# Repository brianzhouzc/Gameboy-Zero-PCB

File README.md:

This is the project page for the Gameboy Zero Button PCB.

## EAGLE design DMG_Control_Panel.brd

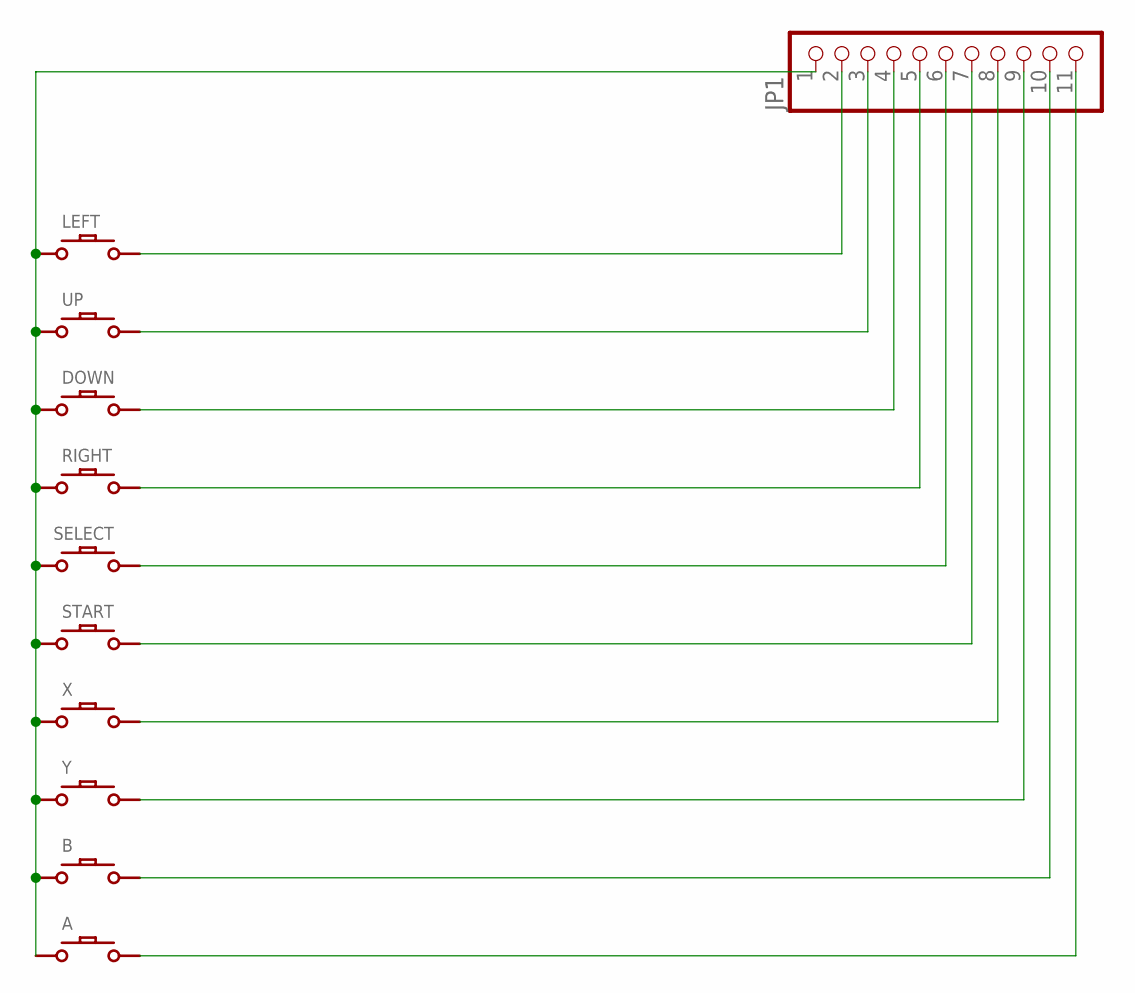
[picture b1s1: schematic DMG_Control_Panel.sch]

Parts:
A: DMG-BTN
B: DMG-BTN
DOWN: DMG-BTN
JP1: PINHD-1X11M; 1X11M
LEFT: DMG-BTN
RIGHT: DMG-BTN
SELECT: DMG-BTN; DMG-SEL
START: DMG-BTN; DMG-SEL
UP: DMG-BTN
X: DMG-BTN
Y: DMG-BTN

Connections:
GND: A.P$1, B.P$1, DOWN.P$1, JP1.1, LEFT.P$1, RIGHT.P$1, SELECT.P$2, START.P$2, UP.P$1, X.P$1, Y.P$1
unnamed: JP1.2, LEFT.P$2
unnamed: JP1.3, UP.P$2
unnamed: DOWN.P$2, JP1.4
unnamed: JP1.5, RIGHT.P$2
unnamed: JP1.6, SELECT.P$1
unnamed: JP1.7, START.P$1
unnamed: JP1.8, X.P$2
unnamed: JP1.9, Y.P$2
unnamed: B.P$2, JP1.10
unnamed: A.P$2, JP1.11

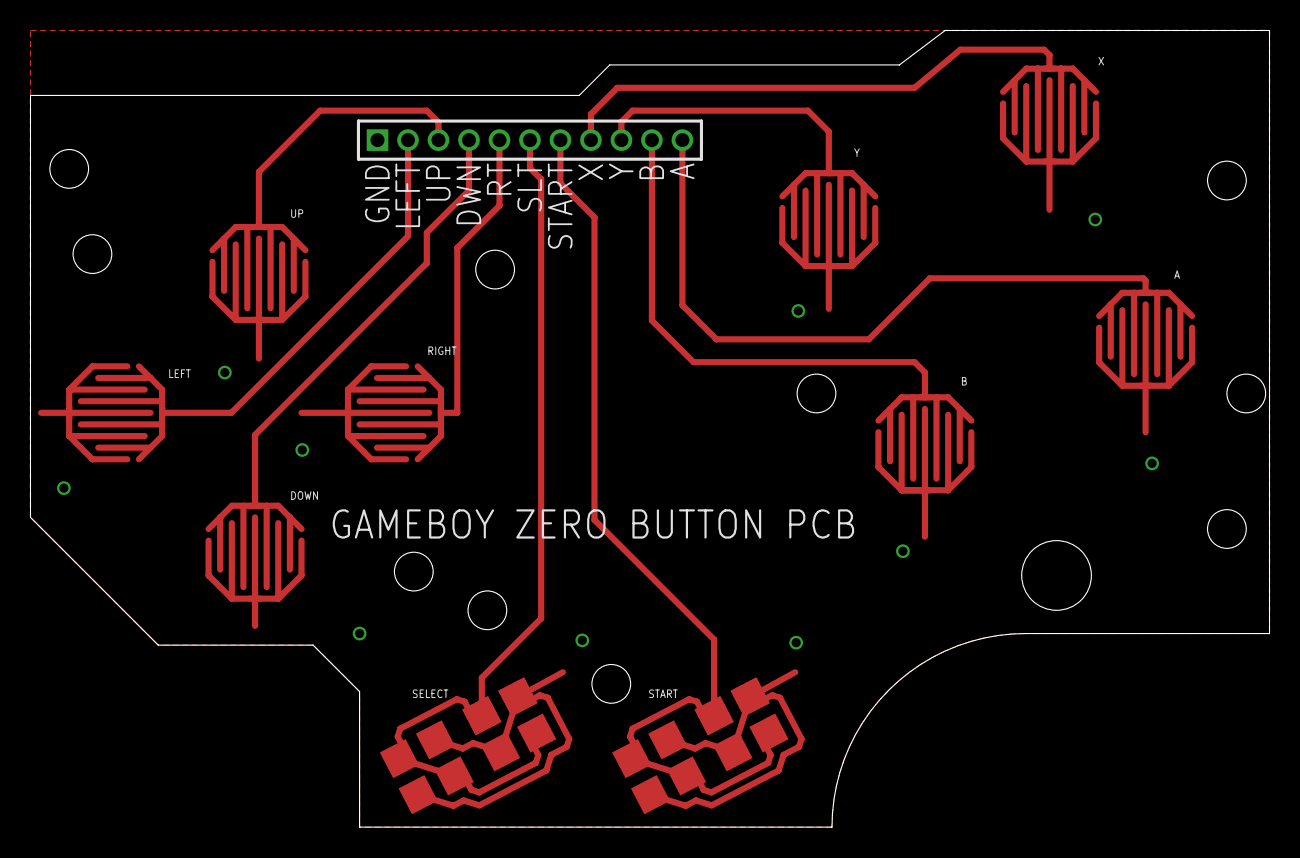
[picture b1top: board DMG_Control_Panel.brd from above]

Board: 2 copper layers, 81.3 x 52.3 mm, 11 parts (0 on the bottom side), 11 nets.

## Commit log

2016-04-28 Readme update
2016-05-05 Added files via upload
